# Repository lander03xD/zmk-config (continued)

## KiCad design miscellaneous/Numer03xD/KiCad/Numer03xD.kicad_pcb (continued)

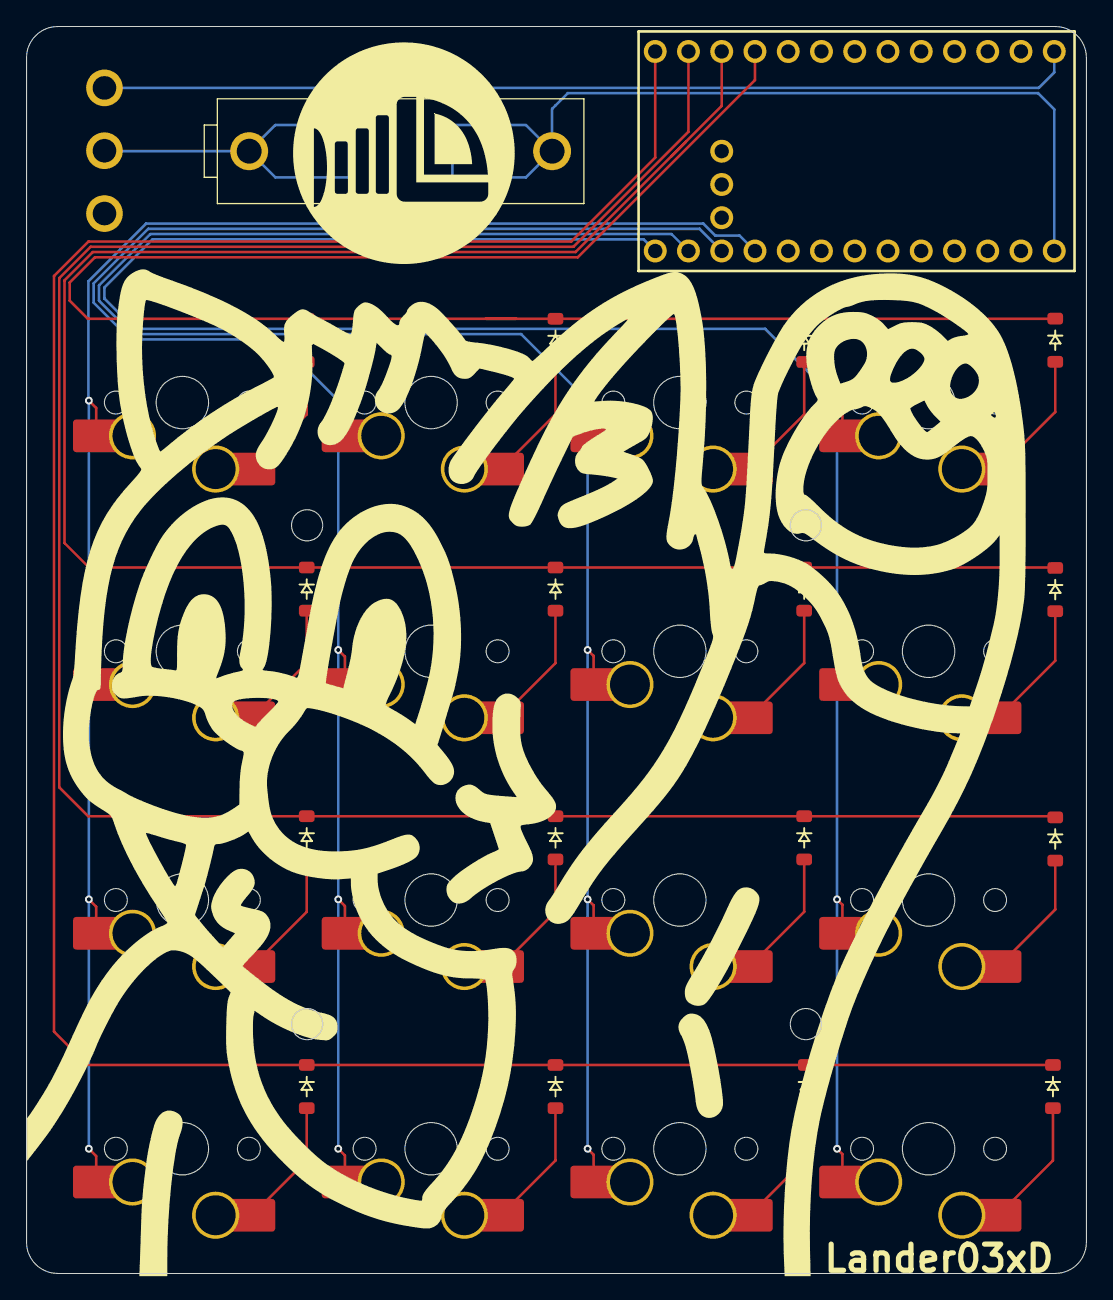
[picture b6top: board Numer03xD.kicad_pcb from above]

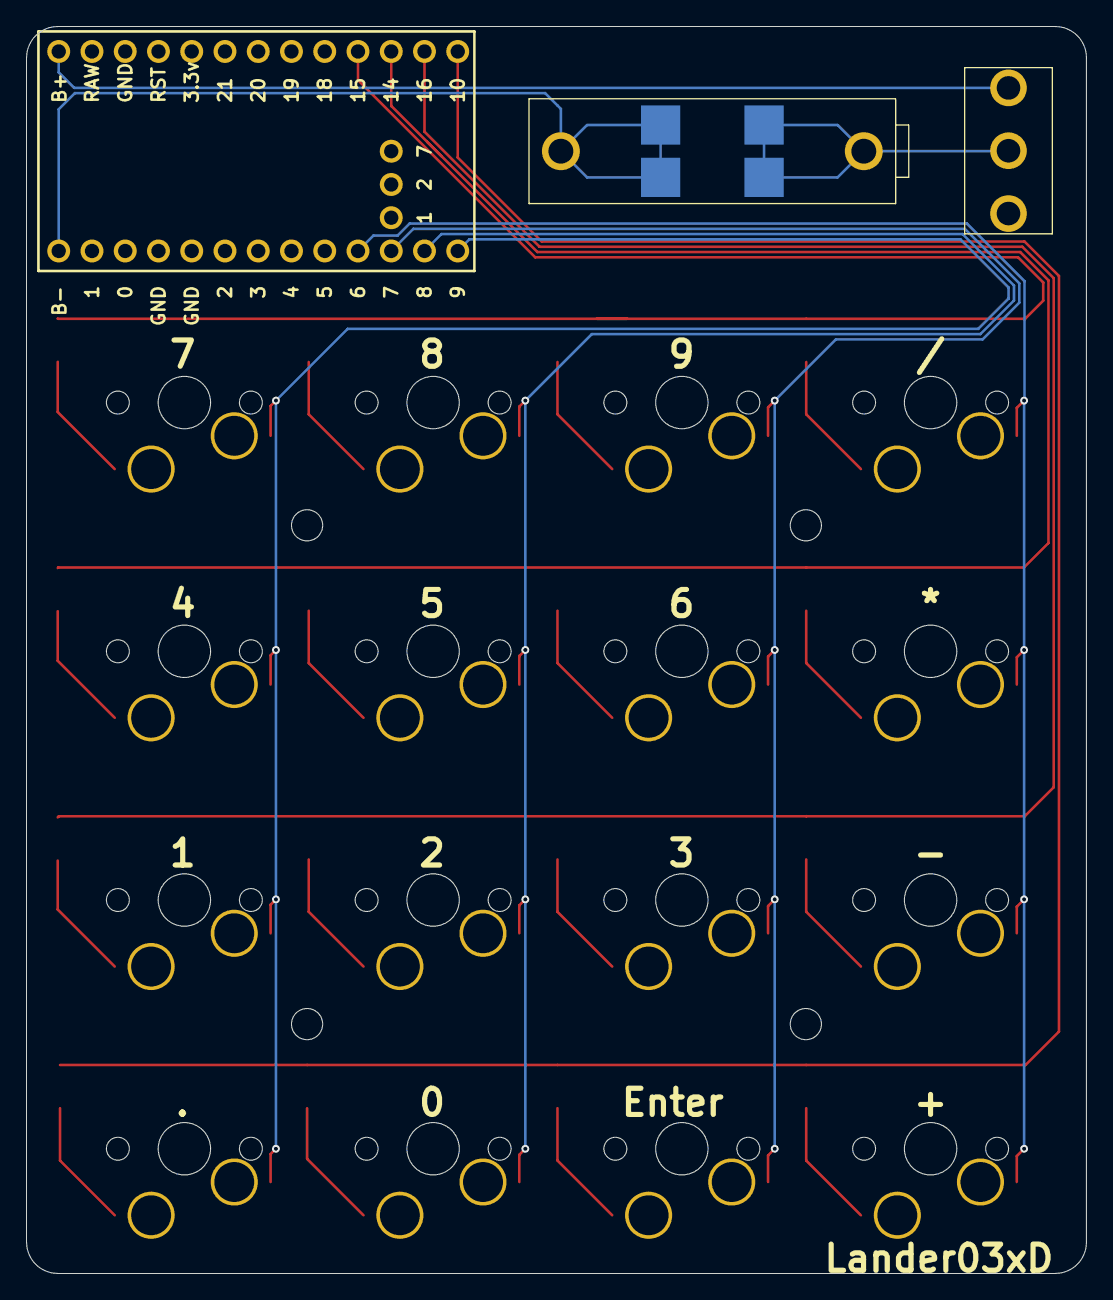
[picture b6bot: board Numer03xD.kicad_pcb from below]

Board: 2 copper layers, 81.0 x 95.3 mm, 35 parts (3 on the bottom side), 27 nets.

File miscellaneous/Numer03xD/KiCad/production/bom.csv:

Designator,Footprint,Quantity,Value,LCSC Part #
BT1,SbM-9202_14250_battery_holder,1,Battery_Cell,
"D1, D10, D11, D12, D13, D14, D15, D16, D2, D3, D4, D5, D6, D7, D8, D9",Diode_SOD-123,16,Diode,
"S1, S10, S11, S12, S13, S14, S15, S16, S2, S3, S4, S5, S6, S7, S8, S9",MX_Hotswap_1.00u,16,Keyswitch,
SW1,SW_Vertical_Slide_5mm,1,SW_SPDT_312,
U1,Promicro_nrf52840,1,Promicro_NRF52840,

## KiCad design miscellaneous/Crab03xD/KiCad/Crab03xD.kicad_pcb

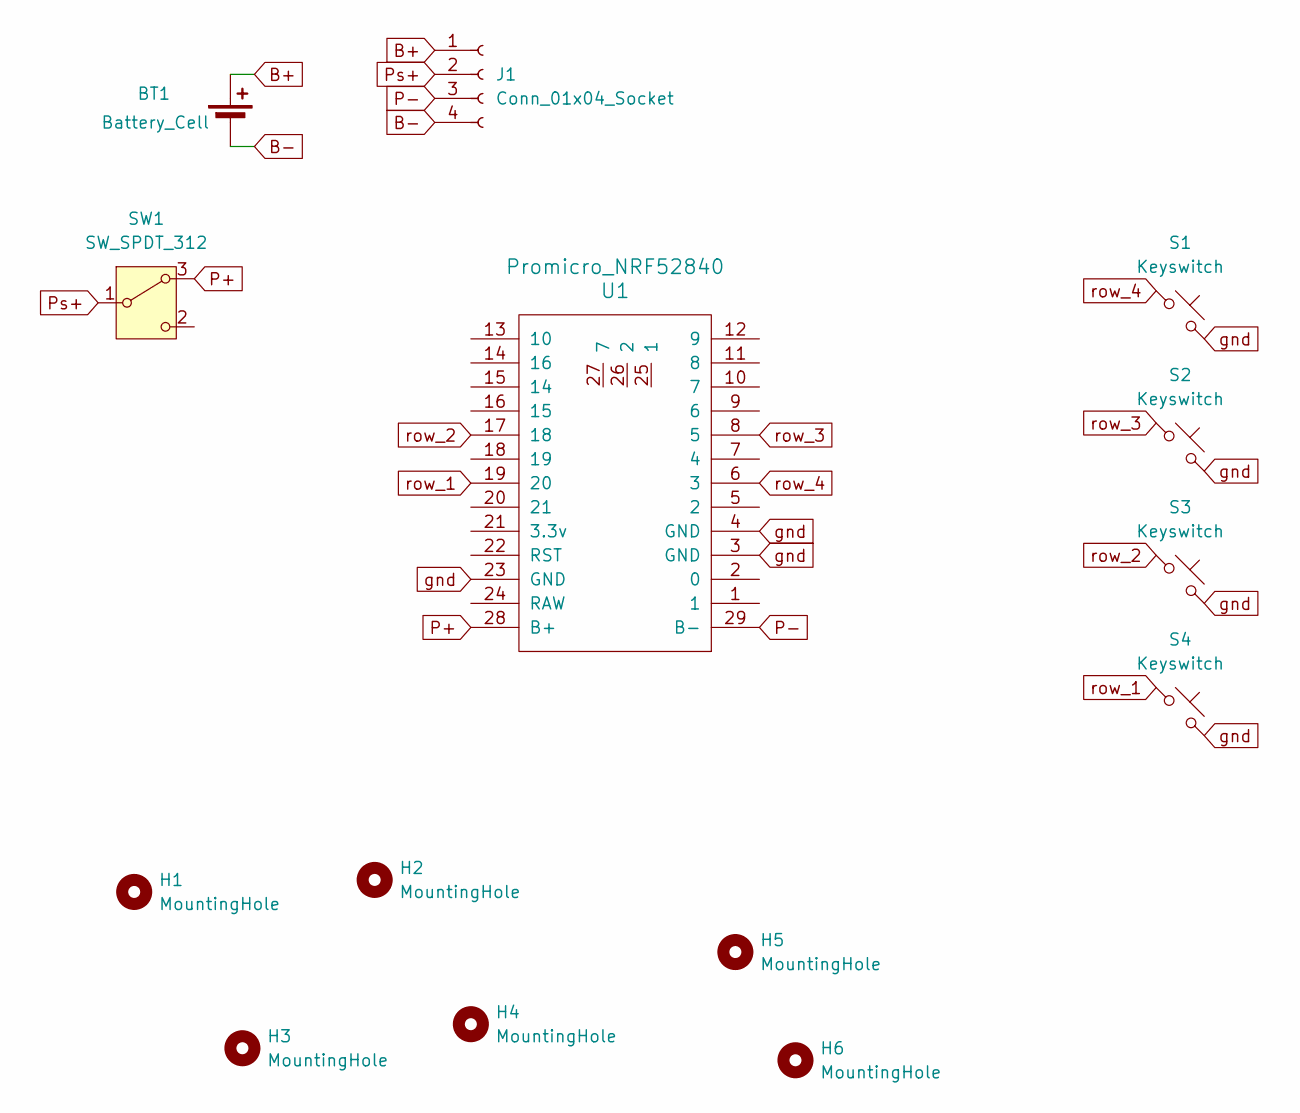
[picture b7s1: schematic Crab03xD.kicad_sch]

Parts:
BT1: Battery_Cell; BatteryHolder_CR2032_20mm
H1, H2, H3, H4, H5, H6: MountingHole; MountingHole_2.2mm_M2
J1: Conn_01x04_Socket; BMS 1S
S1, S2, S3, S4: Keyswitch; Hotswap_MX_1.00u_reversible_18.5mm
SW1: SW_SPDT_312; powerswitch_SK12D07VG
U1: Promicro_NRF52840; Promicro_nrf52840

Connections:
B+: BT1.1 (+), J1.1
B-: BT1.2 (-), J1.4
P+: SW1.3 (A), U1.28 (B+)
P-: J1.3, U1.29 (B-)
Ps+: J1.2, SW1.1 (B)
gnd: S1.2, S2.2, S3.2, S4.2, U1.3 (GND), U1.4 (GND), U1.23 (GND)
row_1: S4.1, U1.19 (20)
row_2: S3.1, U1.17 (18)
row_3: S2.1, U1.8 (5)
row_4: S1.1, U1.6 (3)

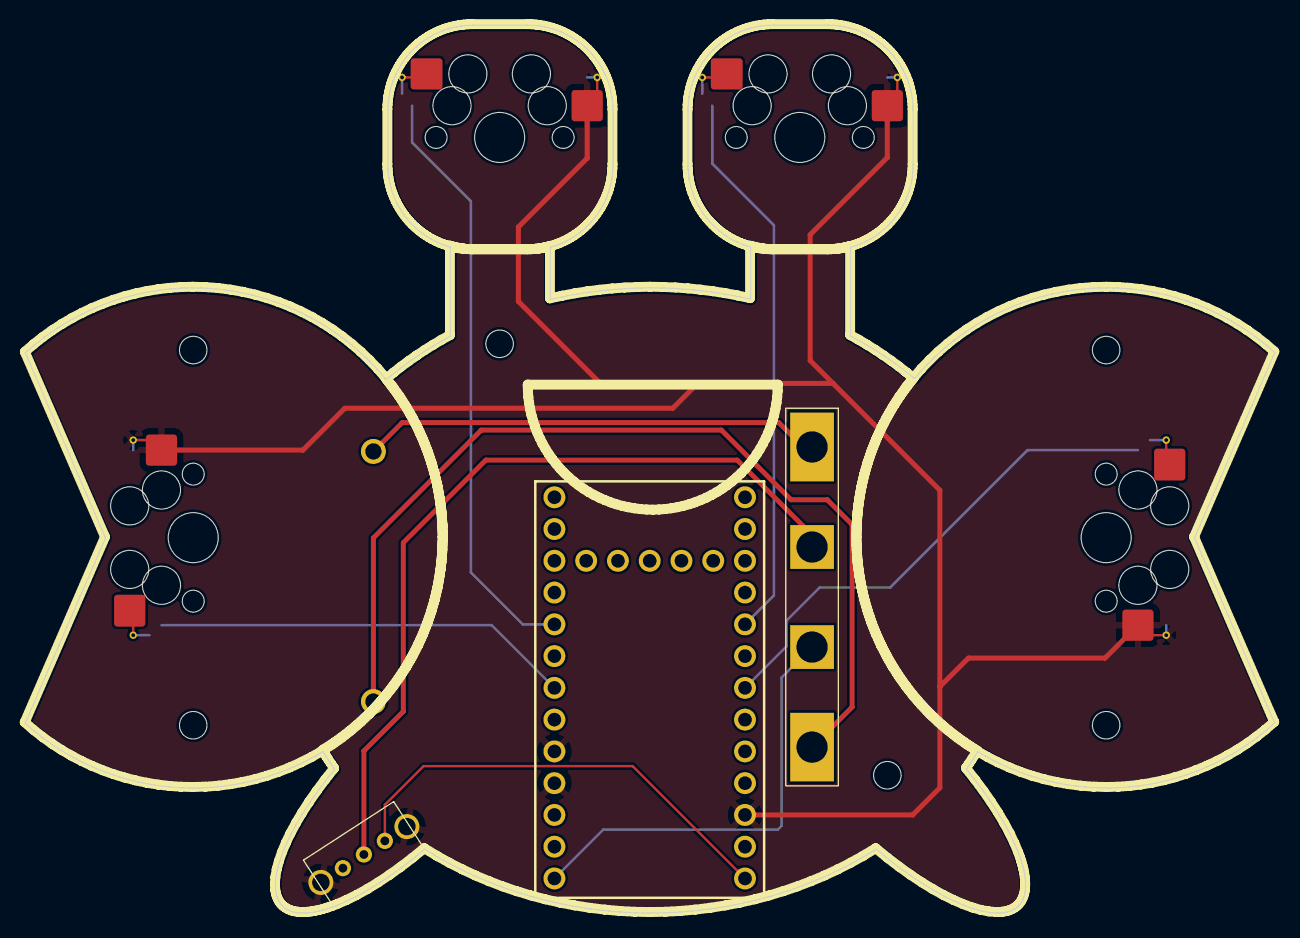
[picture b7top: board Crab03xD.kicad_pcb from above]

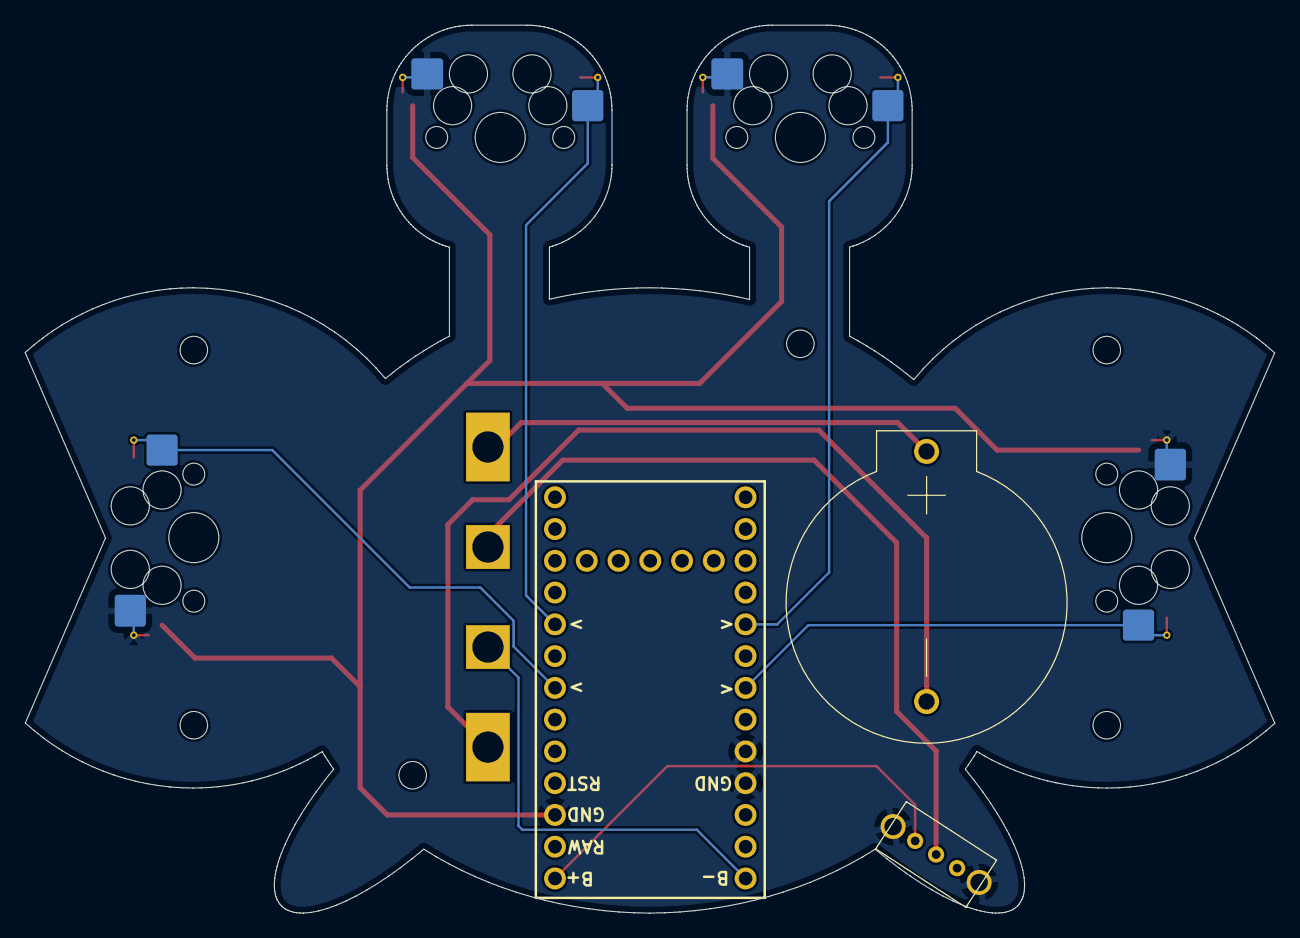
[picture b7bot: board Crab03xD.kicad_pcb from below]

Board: 2 copper layers, 99.9 x 71.0 mm, 14 parts (2 on the bottom side), 10 nets.

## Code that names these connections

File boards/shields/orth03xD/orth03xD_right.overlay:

#include "orth03xD.dtsi" // The shared dtsi file is included in the overlay

// Label of the kscan node in the dtsi
&default_kscan {
    input-gpios =  
        <&gpio0 20 (GPIO_ACTIVE_LOW | GPIO_PULL_UP)>,//Pin_5
        <&gpio0 22 (GPIO_ACTIVE_LOW | GPIO_PULL_UP)>,//Pin_4
	<&gpio0 17 (GPIO_ACTIVE_LOW | GPIO_PULL_UP)>,//Pin_3
	<&gpio0 29 (GPIO_ACTIVE_LOW | GPIO_PULL_UP)>,//Pin_2
	<&gpio0 31 (GPIO_ACTIVE_LOW | GPIO_PULL_UP)>, //Pin_1
			    
        <&gpio1 4 (GPIO_ACTIVE_LOW | GPIO_PULL_UP)>,//Pin_10
	<&gpio1 0 (GPIO_ACTIVE_LOW | GPIO_PULL_UP)>,//Pin_9
	<&gpio1 15 (GPIO_ACTIVE_LOW | GPIO_PULL_UP)>,//Pin_8
	<&gpio0 2 (GPIO_ACTIVE_LOW | GPIO_PULL_UP)>,//Pin_7
	<&gpio0 24 (GPIO_ACTIVE_LOW | GPIO_PULL_UP)>,//Pin_6
			    
	<&gpio1 6  (GPIO_ACTIVE_LOW | GPIO_PULL_UP)>,//Pin_17
	<&gpio0 9 (GPIO_ACTIVE_LOW | GPIO_PULL_UP)>,//Pin_15
	<&gpio0 10  (GPIO_ACTIVE_LOW | GPIO_PULL_UP)>,//Pin_13
	<&gpio1 11 (GPIO_ACTIVE_LOW | GPIO_PULL_UP)>,//Pin_12
	<&gpio1 13 (GPIO_ACTIVE_LOW | GPIO_PULL_UP)>//Pin_11
	;
};

&default_transform { 
    row-offset = <15>;
};

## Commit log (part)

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2026-01-15 make into working github repo
2026-01-15 add Cheap03xD keyboard
2026-01-15 Added complete firmware for cheap03xD
2026-01-15 Added comb03xD files
2026-01-15 add firmware
2026-01-15 Comb03xD firmware
    * Added comb03xD files
    * add firmware
2026-01-16 Macr03xD keyboard files
2026-01-16 Added macr03xD firmware
2026-01-16 added crab03xD miscellaneous folder
2026-01-16 added SplitFish keyboard
2026-01-16 corrected keyboard name in build.yml
2026-01-16 does spacing matter in the yml file
2026-01-16 numer03xD keyboard added
2026-01-16 added firmware for numer03xD
2026-01-16 added FishKeeb
2026-01-16 added steno keyboard
2026-01-16 corrected config after renaming
2026-01-16 correct config for sten03xD
2026-01-16 corrected build file
2026-01-18 added freecad files to sten03xD
2026-01-18 added comb03xD freecad files
2026-01-18 added crab keyboard firmware
2026-01-18 added firmware
2026-01-22 steno firmware updates
2026-01-22 fixed import for zmk studio physical layout
2026-01-22 added firmware for steno board
2026-01-27 right hand side firmware
2026-01-27 build for combo right hand
2026-01-27 firmware changes
2026-01-27 fix layer name duplicate
2026-01-27 correct tapdance names
2026-01-27 imaged comb03xD
2026-05-19 added deep sleep for direct03xD
2026-05-26 code for low3xD keyboard
2026-05-26 keymap correction
2026-05-26 adding proper key name
2026-06-06 changed deep sleep for direct03xD
2026-06-09 build experimental with regregular 36 layout
2026-06-25 low3xD save
2026-06-25 battery sensing for direct03xD
2026-06-25 moved config to config file
2026-06-25 build for the right board
2026-06-25 Batterysensing for Direct03xD (#2)
    * battery sensing for direct03xD
    * moved config to config file
    * build for the right board
2026-06-25 removed usb logging
2026-06-26 moved config to the correct side and remove vbat node
2026-06-26 changed back to default sleep timer except for right deep sleep
2026-06-26 battery optimization attempts for direct03xD
2026-06-26 correct config names
